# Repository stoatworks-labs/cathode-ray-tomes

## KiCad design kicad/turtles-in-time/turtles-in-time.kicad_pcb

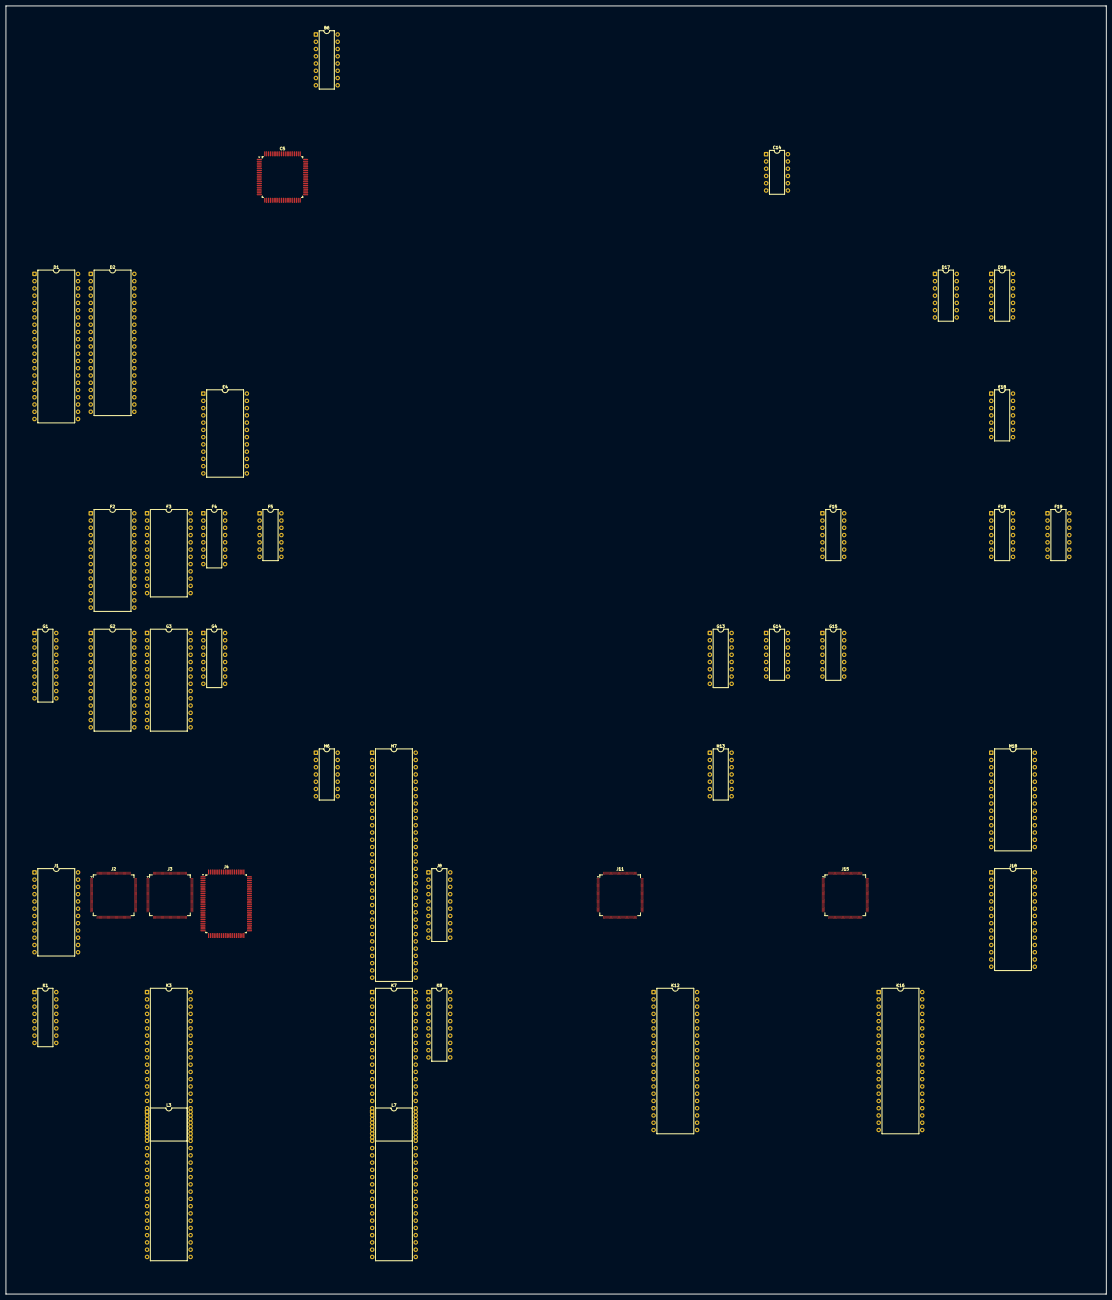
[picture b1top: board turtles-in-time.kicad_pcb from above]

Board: 2 copper layers, 385.2 x 450.9 mm, 43 parts (0 on the bottom side), 406 nets, no tracks yet.

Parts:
B6: YM3012; DIP-16_W7.62mm
C5: 053260; PQFP-80_14x14mm_P0.65mm
C14: MB3722; DIP-12_W7.62mm
D1: 065A08; DIP-42_W15.24mm
D2: Z80CPU; DIP-40_W15.24mm
D17: 74LS00; DIP-14_W7.62mm
D18: 74LS32; DIP-14_W7.62mm
E4: PAL20RS10; DIP-24_W15.24mm
E18: 74LS08; DIP-14_W7.62mm
F2: 27C512; DIP-28_W15.24mm
F3: CY7C128-45PC; DIP-24_W15.24mm
F4: 74LS157; DIP-16_W7.62mm
F5, F15: 74LS74; DIP-14_W7.62mm
F18, F19: 74LS04; DIP-14_W7.62mm
G1: 74LS245; DIP-20_W7.62mm
G2, G3: MB8464A-80-10-15/L-LL; DIP-28_W15.24mm
G4: 74LS157; DIP-16_W7.62mm
G13: 74LS138; DIP-16_W7.62mm
G14: 74LS74; DIP-14_W7.62mm
G15: 74LS08; DIP-14_W7.62mm
H6: LM324; DIP-14_W7.62mm
H7: DIP-64_W15.24mm
H13: 74LS07; DIP-14_W7.62mm
H18: MB8464A-10W-15W; DIP-28_W15.24mm
J1: HM6116P-3; DIP-24_W15.24mm
J2: 053245; TQFP-120_14x14mm_P0.4mm
J3: 053244; TQFP-120_14x14mm_P0.4mm
J4: 053251; PQFP-100_14x20mm_P0.65mm
J8: 74LS245; DIP-20_W7.62mm
J11: 051962; TQFP-120_14x14mm_P0.4mm
J15: 052109; TQFP-120_14x14mm_P0.4mm
J18: MB8464A-10W-15W; DIP-28_W15.24mm
K1: 74LS367; DIP-16_W7.62mm
K3, K7: 065A08; DIP-42_W15.24mm
K8: 74LS245; DIP-20_W7.62mm
K12, K16: 955D05-06-07-08; DIP-40_W15.24mm
L3, L7: 065A08; DIP-42_W15.24mm

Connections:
/M6: J2.10, J3.10, J4.41, J11.78
/M12: J2.12, J3.12, J11.95
/MAIN_A1: G4.2, G15.2, H7.30, J4.85, J11.88, J15.66
/MAIN_A2: G4.5, H7.29, J2.25, J3.18, J4.84, J11.89, J15.67
/MAIN_A3: G4.11, H7.28, J2.24, J3.17, J4.83, J15.68
/MAIN_A4: G4.14, H7.27, J2.23, J3.15, J4.82, J15.69
/MAIN_A5: F4.2, G15.5, H7.24, J15.116
/MAIN_A6: F4.5, G15.10, H7.23, J15.115
/MAIN_A7: H7.22, J2.22, J15.114
/MAIN_A8: G13.1, H7.21, J2.20, J15.113
/MAIN_A9: G13.2, H7.20, J2.19, J15.112
/MAIN_A10: G13.3, H7.19, J2.18, J15.111
/MAIN_A11: E18.9, G13.4, H7.17, J2.17, J15.110
/MAIN_A12: H7.16, J2.15, J15.109
/MAIN_A13: H7.15, J2.14, J15.80
/MAIN_A14: H7.14, J15.81
/MAIN_A15: H7.13, J15.82
/MAIN_DB0: C5.8, J3.29, J4.80, J11.79, J15.56
/MAIN_DB1: C5.9, J3.28, J4.79, J11.80, J15.57
/MAIN_DB2: C5.10, J3.27, J4.77, J11.81, J15.58
/MAIN_DB3: C5.11, J3.26, J4.76, J11.82, J15.59
/MAIN_DB4: C5.13, J3.25, J4.75, J11.83, J15.60
/MAIN_DB5: C5.14, J3.24, J4.74, J11.84, J15.62
/MAIN_DB6: C5.15, J3.23, J15.63
/MAIN_DB7: C5.16, J3.22, J11.86, J15.64
/MRW: D18.2, E18.12
/M~RD: F4.11, G1.1, J2.13, J3.20, J11.87, J15.85
/OBJ~SET: D17.1, E18.13, J2.6, J3.13
/PDS: E18.10, F15.4, G13.6
/RM~RD: J11.96, J15.97
/SCR~CLK: J11.90, J15.65
/colmix/ACOL0: J4.57, J11.30
/colmix/ACOL1: J4.58, J11.32
/colmix/ACOL2: J4.59, J11.33
/colmix/ACOL3: J4.60, J11.34
/colmix/APAL0: J4.61, J11.36
/colmix/APAL1: J4.62, J11.37
/colmix/APAL2: J4.63, J11.38
/colmix/BCOL0: J4.66, J11.46
/colmix/BCOL1: J4.67, J11.47
/colmix/BCOL2: J4.68, J11.48
/colmix/BCOL3: J4.69, J11.49
/colmix/BPAL0: J4.70, J11.51
/colmix/BPAL1: J4.71, J11.52
/colmix/BPAL2: J4.72, J11.53
/colmix/FCOL0: J4.47, J11.59
/colmix/FCOL1: J4.48, J11.60
/colmix/FCOL2: J4.49, J11.62
/colmix/FCOL3: J4.50, J11.63
/colmix/FPAL0: J4.51, J11.65
/colmix/FPAL1: J4.52, J11.66
/colmix/OCOL0: J3.120, J4.30
/colmix/OCOL1: J3.119, J4.31
/colmix/OCOL2: J3.118, J4.32
/colmix/OCOL3: J3.117, J4.33
/colmix/OCOL4: J3.116, J4.34
/colmix/OCOL5: J3.115, J4.35
/colmix/OCOL6: J3.114, J4.36
/colmix/OCOL7: J3.113, J4.37
/colmix/OCOL8: J3.112, J4.38
/colmix/PCU~CS: G13.7, J4.81
/colmix/PR12: J3.110, J4.25
/colmix/PR13: J3.109, J4.27
/colmix/SDI0: J3.108, J4.95
/main2obj/MPDS: D17.5, E18.8
/main2obj/RD0: G3.11, J2.45, K8.2
/main2obj/RD1: G3.12, J2.44, K8.3
/main2obj/RD2: G3.13, J2.43, K8.4
/main2obj/RD3: G3.15, J2.42, K8.5
/main2obj/RD4: G3.16, J2.40, K8.6
/main2obj/RD5: G3.17, J2.39, K8.7
/main2obj/RD6: G3.18, J2.38, K8.8
/main2obj/RD7: G3.19, J2.37, K8.9
/main2obj/RD8: G2.19, J2.35, J8.2
/main2obj/RD9: G2.18, J2.34, J8.3
/main2obj/RD10: G2.17, J2.33, J8.4
/main2obj/RD11: G2.16, J2.32, J8.5
/main2obj/RD12: G2.15, J2.30, J8.6
/main2obj/RD13: G2.13, J2.29, J8.7
/main2obj/RD14: G2.12, J2.28, J8.8
/main2obj/RD15: G2.11, J2.27, J8.9
/main2obj/RDB0: H7.31, K8.18
/main2obj/RDB1: H7.32, K8.17
/main2obj/RDB2: H7.33, K8.16
/main2obj/RDB3: H7.35, K8.15
/main2obj/RDB4: H7.36, K8.14
/main2obj/RDB5: H7.37, K8.13
/main2obj/RDB6: H7.38, K8.12
/main2obj/RDB7: H7.39, K8.11
/main2obj/RDB8: H7.40, J8.18
/main2obj/RDB9: H7.43, J8.17
/main2obj/RDB10: H7.44, J8.16
/main2obj/RDB11: H7.45, J8.15
/main2obj/RDB12: H7.46, J8.14
/main2obj/RDB13: H7.47, J8.13
/main2obj/RDB14: H7.48, J8.12
/main2obj/RDB15: H7.49, J8.11
/objects/AR0: J2.119, J3.30
/objects/AR1: J2.118, J3.32
/objects/AR2: J2.117, J3.33
/objects/AROK: J2.116, J3.34
/objects/BK0: G1.18, J1.9, K1.3, K3.36, K7.36, L3.36, L7.36
/objects/BK1: G1.17, J1.10, K1.5, K3.35, K7.35, L3.35, L7.35
/objects/BK2: G1.16, J1.11, K1.7, K3.34, K7.34, L3.34, L7.34
/objects/BK3: G1.15, J1.13, K1.9, K3.33, K7.33, L3.33, L7.33
/objects/BK4: G1.14, J1.14, K1.11, K3.2, K7.2, L3.2, L7.2
/objects/BK5: G1.13, J1.15, K1.13, K3.1, K7.1, L3.1, L7.1
/objects/BK6: F18.9, G1.12, J1.16
/objects/BK7: G1.11, J1.17
/objects/BR0: J2.115, J3.35
/objects/BR1: J2.114, J3.36
/objects/BR2: J2.113, J3.37
/objects/BROK: J2.112, J3.38
/objects/CLAT: J2.86, J3.64
/objects/HP0: J2.96, J3.54
/objects/HP1: J2.97, J3.53
/objects/HP2: J2.98, J3.52
/objects/HP3: J2.99, J3.50
/objects/HP4: J2.100, J3.49
/objects/HP5: J2.102, J3.48
/objects/HP6: J2.103, J3.47
/objects/HP7: J2.104, J3.45
/objects/HP8: J2.105, J3.44
/objects/HP9: J2.107, J3.43
/objects/HRFP: J2.110, J3.39
/objects/MDB6: L3.13, L7.13
/objects/OBJMPX: D17.9, F19.12, G15.1, G15.4, G15.9
/objects/OBJROMA0: J2.85, K3.10, K7.10, L3.10, L7.10
/objects/OBJROMA1: J2.84, K3.9, K7.9, L3.9, L7.9
/objects/OBJROMA2: J2.83, K3.8, K7.8, L3.8, L7.8
/objects/OBJROMA3: J2.82, K3.7, K7.7, L3.7, L7.7
/objects/OBJROMA4: J2.80, K3.6, K7.6, L3.6, L7.6
/objects/OBJROMA5: J2.79, K3.5, K7.5, L3.5, L7.5
/objects/OBJROMA6: J2.78, K3.4, K7.4, L3.4, L7.4
/objects/OBJROMA7: J2.77, K3.3, K7.3, L3.3, L7.3
/objects/OBJROMA8: J2.75, K3.41, K7.41, L3.41, L7.41
/objects/OBJROMA9: J2.74, K3.40, K7.40, L3.40, L7.40
/objects/OBJROMA10: J2.73, K3.39, K7.39, L3.39, L7.39
/objects/OBJROMA11: J2.72, K3.38, K7.38, L3.38, L7.38
/objects/OBJROMA12: J2.70, K3.37, K7.37, L3.37, L7.37
/objects/OBJROMA13: G4.3, J2.69, K1.2
/objects/OBJROMA14: G4.6, J2.68, K1.4
/objects/OBJROMA15: G4.10, J2.67, K1.6
/objects/OBJROMA16: G4.13, J2.66, K1.10
/objects/OBJROMA17: F4.3, J2.65, K1.12
/objects/OBJROMA18: F4.6, J2.64, K1.14
/objects/OBJROMD0: J3.100, K7.14, L7.14
/objects/OBJROMD1: J3.99, K7.16, L7.16
/objects/OBJROMD2: J3.98, K7.18, L7.18
/objects/OBJROMD3: J3.97, K7.20, L7.20
/objects/OBJROMD4: J3.96, K7.23, L7.23
/objects/OBJROMD5: J3.95, K7.25, L7.25
/objects/OBJROMD6: J3.94, K7.27, L7.27
/objects/OBJROMD7: J3.93, K7.29, L7.29
/objects/OBJROMD8: J3.92, K7.15, L7.15
/objects/OBJROMD9: J3.90, K7.17, L7.17
/objects/OBJROMD10: J3.89, K7.19, L7.19
/objects/OBJROMD11: J3.88, K7.21, L7.21
/objects/OBJROMD12: J3.87, K7.24, L7.24
/objects/OBJROMD13: J3.86, K7.26, L7.26
/objects/OBJROMD14: J3.85, K7.28, L7.28
/objects/OBJROMD15: J3.84, K7.30, L7.30
/objects/OBJROMD16: J3.83, K3.14, L3.14
/objects/OBJROMD17: J3.82, K3.16, L3.16
/objects/OBJROMD18: J3.80, K3.18, L3.18
/objects/OBJROMD19: J3.79, K3.20, L3.20
/objects/OBJROMD20: J3.78, K3.23, L3.23
/objects/OBJROMD21: J3.77, K3.25, L3.25
/objects/OBJROMD22: J3.75, K3.27, L3.27
/objects/OBJROMD23: J3.74, K3.29, L3.29
/objects/OBJROMD24: J3.73, K3.15, L3.15
/objects/OBJROMD25: J3.72, K3.17, L3.17
/objects/OBJROMD26: J3.70, K3.19, L3.19
/objects/OBJROMD27: J3.69, K3.21, L3.21
/objects/OBJROMD28: J3.68, K3.24, L3.24
/objects/OBJROMD29: J3.67, K3.26, L3.26
/objects/OBJROMD30: J3.66, K3.28, L3.28
/objects/OBJROMD31: J3.65, K3.30, L3.30
/objects/PL0: J2.87, J3.63
/objects/PL1: J2.88, J3.62
/objects/PL2: J2.89, J3.60
/objects/PL3: J2.90, J3.59
/objects/PL4: J2.92, J3.58
/objects/PL5: J2.93, J3.57
/objects/PL6: J2.94, J3.56
/objects/RA0: G2.10, G3.10, G15.3
/objects/RA1: G2.9, G3.9, J2.52
/objects/RA2: G2.8, G3.8, J2.53
/objects/RA3: G2.7, G3.7, J2.54
/objects/RA4: G2.6, G3.6, G15.6
/objects/RA5: G2.5, G3.5, G15.8
/objects/RA6: G2.4, G3.4, J2.55
/objects/RA7: G2.3, G3.3, J2.56
/objects/RA8: G2.25, G3.25, J2.57
/objects/RA9: G2.24, G3.24, J2.58
/objects/RA10: G2.21, G3.21, J2.59
/objects/RA11: G2.23, G3.23, J2.62
/objects/RA12: G2.2, G3.2, J2.63
/objects/R~OE: G2.22, G3.22, J2.49
/objects/SHADOW: J2.95, J3.55
/objects/~BK6: F18.8, K3.13
/objects/~HIT: J2.108, J3.42
/objects/~WE1: G2.27, J2.48
/objects/~WE2: G3.27, J2.47
/objects/~ZLD: J2.109, J3.40
/pcm_snd/AUX2: C5.24, D1.13
/pcm_snd/PCM~CS: C5.72, E4.19
/pcm_snd/RA0: C5.39, D1.30
/pcm_snd/RA1: C5.40, D1.10
/pcm_snd/RA2: C5.41, D1.9
/pcm_snd/RA3: C5.42, D1.8
/pcm_snd/RA4: C5.44, D1.7
/pcm_snd/RA5: C5.45, D1.6
/pcm_snd/RA6: C5.46, D1.5
/pcm_snd/RA8: C5.48, D1.3
/pcm_snd/RA9: C5.49, D1.41
/pcm_snd/RA10: C5.50, D1.40
/pcm_snd/RA11: C5.51, D1.39
/pcm_snd/RA12: C5.53, D1.38
/pcm_snd/RA13: C5.54, D1.37
/pcm_snd/RA14: C5.55, D1.36
/pcm_snd/RA15: C5.56, D1.35
/pcm_snd/RA16: C5.57, D1.34
/pcm_snd/RA17: C5.58, D1.33
/pcm_snd/RA20: C5.62, D1.42
/pcm_snd/RD0: C5.29, D1.14
/pcm_snd/RD1: C5.30, D1.16
/pcm_snd/RD2: C5.31, D1.18
/pcm_snd/RD3: C5.32, D1.20
/pcm_snd/RD4: C5.35, D1.23
/pcm_snd/RD5: C5.36, D1.25
/pcm_snd/RD6: C5.37, D1.27
/pcm_snd/RD7: C5.38, D1.29
/pcm_snd/SH1: B6.6, C5.26, F5.11
/pcm_snd/SH2: B6.5, C5.27
/pcm_snd/SND_A0: C5.70, D2.30, E4.8, F2.10, F3.8
/pcm_snd/SND_A1: C5.69, D2.31, E4.7, F2.9, F3.7
/pcm_snd/SND_A2: C5.68, D2.32, E4.6, F2.8, F3.6
/pcm_snd/SND_A3: C5.67, D2.33, F2.7, F3.5
/pcm_snd/SND_A4: C5.66, D2.34, F2.6, F3.4
/pcm_snd/SND_A5: C5.65, D2.35, F2.5, F3.3
/pcm_snd/SND_D0: C5.5, F2.11, F3.9
/pcm_snd/SND_D1: C5.4, F2.12, F3.10
/pcm_snd/SND_D2: C5.3, D2.12, F2.13, F3.11
/pcm_snd/SND_D3: C5.2, D2.8, D2.14, F2.15, F3.13
/pcm_snd/SND_D4: C5.1, D2.15, F2.16, F3.14
/pcm_snd/SND_D5: C5.80, D2.9, F2.17, F3.15
/pcm_snd/SND_D6: C5.79, D2.10, F2.18, F3.16
/pcm_snd/SND_D7: C5.78, D2.13, D2.18, F2.19, F3.17
/pcm_snd/SY: B6.2, C5.25
/scroll/COL5: J11.109, J15.42
/scroll/COL6: J11.108, J15.43
/scroll/COL7: J11.107, J15.46
/scroll/GFXROMA0: J15.35, K12.9, K16.9
/scroll/GFXROMA1: J15.34, K12.8, K16.8
/scroll/GFXROMA2: J15.33, K12.7, K16.7
/scroll/GFXROMA3: J15.32, K12.6, K16.6
/scroll/GFXROMA4: J15.30, K12.5, K16.5
/scroll/GFXROMA5: J15.29, K12.4, K16.4
/scroll/GFXROMA6: J15.28, K12.3, K16.3
/scroll/GFXROMA7: J15.27, K12.2, K16.2
/scroll/GFXROMA8: J15.26, K12.40, K16.40
/scroll/GFXROMA9: J15.25, K12.39, K16.39
/scroll/GFXROMA10: J15.24, K12.38, K16.38
/scroll/GFXROMA11: J15.37, K12.37, K16.37
/scroll/GFXROMA12: J15.38, K12.36, K16.36
/scroll/GFXROMA13: J15.41, K12.35, K16.35
/scroll/GFXROMA14: J15.39, K12.34, K16.34
/scroll/GFXROMA15: J15.40, K12.33, K16.33
/scroll/GFXROMA16: J15.23, K12.32, K16.32
/scroll/GFXROMA17: J15.22, K12.1, K16.1
/scroll/GFXROMD0: J11.29, K16.13
/scroll/GFXROMD1: J11.28, K16.15
/scroll/GFXROMD2: J11.27, K16.17
/scroll/GFXROMD3: J11.26, K16.19
/scroll/GFXROMD4: J11.25, K16.22
/scroll/GFXROMD5: J11.24, K16.24
/scroll/GFXROMD6: J11.23, K16.26
/scroll/GFXROMD7: J11.22, K16.28
/scroll/GFXROMD8: J11.21, K16.14
/scroll/GFXROMD9: J11.20, K16.16
/scroll/GFXROMD10: J11.19, K16.18
/scroll/GFXROMD11: J11.18, K16.20
/scroll/GFXROMD12: J11.17, K16.23
/scroll/GFXROMD13: J11.16, K16.25
/scroll/GFXROMD14: J11.13, K16.27
/scroll/GFXROMD15: J11.12, K16.29
/scroll/GFXROMD16: J11.11, K12.13
/scroll/GFXROMD17: J11.10, K12.15
/scroll/GFXROMD18: J11.9, K12.17
/scroll/GFXROMD19: J11.8, K12.19
/scroll/GFXROMD20: J11.7, K12.22
/scroll/GFXROMD21: J11.6, K12.24
/scroll/GFXROMD22: J11.5, K12.26
/scroll/GFXROMD23: J11.4, K12.28
/scroll/GFXROMD24: J11.3, K12.14
/scroll/GFXROMD25: J11.2, K12.16
/scroll/GFXROMD26: J11.120, K12.18
/scroll/GFXROMD27: J11.119, K12.20
/scroll/GFXROMD28: J11.118, K12.23
/scroll/GFXROMD29: J11.117, K12.25
/scroll/GFXROMD30: J11.116, K12.27
/scroll/GFXROMD31: J11.115, K12.29
/scroll/SCRAMA0: H18.10, J15.2, J18.10
/scroll/SCRAMA1: H18.9, J15.120, J18.9
/scroll/SCRAMA2: H18.8, J15.119, J18.8
/scroll/SCRAMA3: H18.7, J15.118, J18.7
/scroll/SCRAMA4: H18.6, J15.117, J18.6
/scroll/SCRAMA5: H18.5, J15.70, J18.5
/scroll/SCRAMA6: H18.4, J15.71, J18.4
/scroll/SCRAMA7: H18.3, J15.72, J18.3
/scroll/SCRAMA8: H18.25, J15.73, J18.25
/scroll/SCRAMA9: H18.24, J15.76, J18.24
/scroll/SCRAMA10: H18.21, J15.77, J18.21
/scroll/SCRAMA11: H18.23, J15.78, J18.23
/scroll/SCRAMA12: H18.2, J15.79, J18.2
/scroll/VD0: H18.11, J15.20
/scroll/VD1: H18.12, J15.19
/scroll/VD2: H18.13, J15.18
/scroll/VD3: H18.15, J15.17
/scroll/VD4: H18.16, J15.16
/scroll/VD5: H18.17, J15.13
/scroll/VD6: H18.18, J15.12
/scroll/VD7: H18.19, J15.11
/scroll/VD8: J15.10, J18.11
/scroll/VD9: J15.9, J18.12
/scroll/VD10: J15.8, J18.13
/scroll/VD11: J15.7, J18.15
/scroll/VD12: J15.6, J18.16
/scroll/VD13: J15.5, J18.17
/scroll/VD14: J15.4, J18.18
/scroll/VD15: J15.3, J18.19
/scroll/ZA1H: J11.101, J15.50
/scroll/ZA2H: J11.100, J15.51
/scroll/ZA4H: J11.99, J15.52
/scroll/ZB1H: J11.106, J15.47
/scroll/ZB2H: J11.103, J15.48
/scroll/ZB4H: J11.102, J15.49
/scroll/~BE: J11.98, J15.53
/scroll/~RCS1: J15.93, J18.20
/scroll/~ROE1: J15.95, J18.22
/scroll/~ROE2: H18.22, J15.96
/scroll/~RWE1: J15.107, J18.27
/scroll/~RWE2: H18.27, J15.108
/sound/ROM~OE: E4.16, F2.22
/sound/SND_A6: D2.36, F2.4, F3.2
/sound/SND_A7: D2.37, F2.3, F3.1
/sound/SND_A8: D2.38, F2.25, F3.23
/sound/SND_A9: D2.39, E4.14, F2.24, F3.22
/sound/SND_A10: D2.40, E4.13, F2.21, F3.19
/sound/SND_A11: E4.11, F2.23
/sound/SND_A12: D2.2, E4.9, F2.2
/sound/SND_A14: D2.4, F2.27
/sound/SRAM~CE: E4.17, F3.18
/sound/S~CLK: G14.5, G14.11
/sound/S~IORQ: D2.20, G15.13
/sound/S~RD: D2.6, D2.21, F3.20, F19.3
/sound/S~WR: D2.5, E4.5, F3.21
/sound/~M1: D2.27, E4.3
/sound/~RFSH: D2.28, E4.2
/sound/~WAIT: D2.24, G14.9
/sound/~WSET: E4.15, G14.10
/~AS: E4.4, H7.1
/~HSYNC: J2.4, J3.8, J11.73
/~LDS: H7.63, J2.9
/~OBJ: D17.2, D18.1, E4.21
/~OVRC: F4.1, G1.19, G4.1, G13.10
/~RESET: J2.3, J3.3, J11.92, J15.55
/~SYSRES: B6.7, C5.75, D2.3, D2.26, F5.13, G15.12, H7.59, H13.8
/~UDS: H7.62, J2.8, J3.19
/~VRAM: J11.97, J15.54, J15.84
/~VSYNC: J2.5, J3.9, J11.72
GND: E4.10, E4.12, F15.2
unnamed: B6.14, H6.2
unnamed: B6.12, H6.10
unnamed: B6.9, B6.10, H6.5, H6.12
unnamed: B6.13, H6.1
unnamed: B6.15, H6.3
unnamed: C5.71, F19.4
unnamed: D2.7, E4.18
unnamed: D2.16, F5.6
unnamed: D2.17, F5.9
unnamed: D17.3, D17.10
unnamed: E4.1, F15.5
unnamed: F4.4, J1.4
unnamed: F4.7, J1.3
unnamed: F4.9, J1.20
unnamed: F4.12, J1.21
unnamed: F5.1, G15.11
unnamed: G4.4, J1.8
unnamed: G4.7, J1.7
unnamed: G4.9, J1.6
unnamed: G4.12, J1.5
unnamed: G14.2, G14.6
unnamed: G14.8, G14.12
unnamed: H6.6, H6.7
unnamed: H6.8, H6.9
unnamed: H6.13, H6.14
unnamed: D17.6, H7.54
unnamed: H13.9, J15.98
unnamed: F19.13, J2.26
unnamed: D18.3, J2.7
unnamed: E18.11, J8.1, K8.1
unnamed: D17.8, J8.19, K8.19
VCC: B6.1, C5.20, C5.33, C5.73, D1.4, D1.11, D1.22, D1.31, D2.22, E4.20, E4.24, F2.28, F3.24, F4.13, F5.2, F5.4, F15.1, G2.26, G2.28, G3.26, G3.28, G14.1, G14.4, G14.13, H7.9, H7.26, H7.41, H7.58, H18.26, H18.28, J1.24, J2.16, J2.46, J2.60, J2.76, J2.106, J2.120, J3.16, J3.46, J3.76, J3.106, J4.1, J4.2, J4.3, J4.28, J4.29, J4.39, J4.42, J4.43, J4.44, J4.45, J4.46, J4.53, J4.78, J4.97, J4.98, J4.99, J4.100, J11.14, J11.44, J11.74, J11.104, J15.14, J15.44, J15.74, J15.104, J18.26, J18.28, K1.16, K3.22, K3.31, K3.32, K7.22, K7.31, K7.32, K12.21, K12.31, K16.21, K16.31, L3.22, L3.31, L3.32, L7.22, L7.31, L7.32
VSS: B6.3, B6.8, B6.16, C5.12, C5.34, C5.43, C5.52, C5.61, C5.74, C14.6, C14.7, D1.1, D1.2, D1.12, D1.32, D2.1, D2.11, D2.29, F2.14, F3.12, F4.10, F4.15, F5.12, G2.14, G2.20, G3.14, G3.20, G4.15, H7.2, H7.10, H7.18, H7.25, H7.34, H7.42, H7.50, H7.55, H7.57, H18.14, H18.20, J1.12, J1.18, J1.19, J1.22, J2.1, J2.2, J2.11, J2.21, J2.31, J2.41, J2.51, J2.61, J2.71, J2.81, J2.91, J2.101, J2.111, J3.1, J3.2, J3.4, J3.5, J3.6, J3.7, J3.11, J3.21, J3.31, J3.41, J3.51, J3.61, J3.71, J3.81, J3.91, J3.101, J3.111, J4.4, J4.5, J4.6, J4.7, J4.8, J4.9, J4.10, J4.15, J4.20, J4.21, J4.22, J4.23, J4.24, J4.40, J4.55, J4.56, J4.64, J4.65, J4.73, J4.90, J4.94, J11.1, J11.15, J11.31, J11.45, J11.61, J11.75, J11.91, J11.94, J11.105, J11.110, J11.111, J11.112, J11.113, J11.114, J15.1, J15.15, J15.21, J15.31, J15.36, J15.45, J15.61, J15.75, J15.91, J15.105, J18.14, K1.1, K1.8, K1.15, K3.11, K3.12, K7.11, K7.12, K12.10, K12.11, K12.12, K12.30, K16.10, K16.11, K16.12, K16.30, L3.11, L3.12, L7.11, L7.12

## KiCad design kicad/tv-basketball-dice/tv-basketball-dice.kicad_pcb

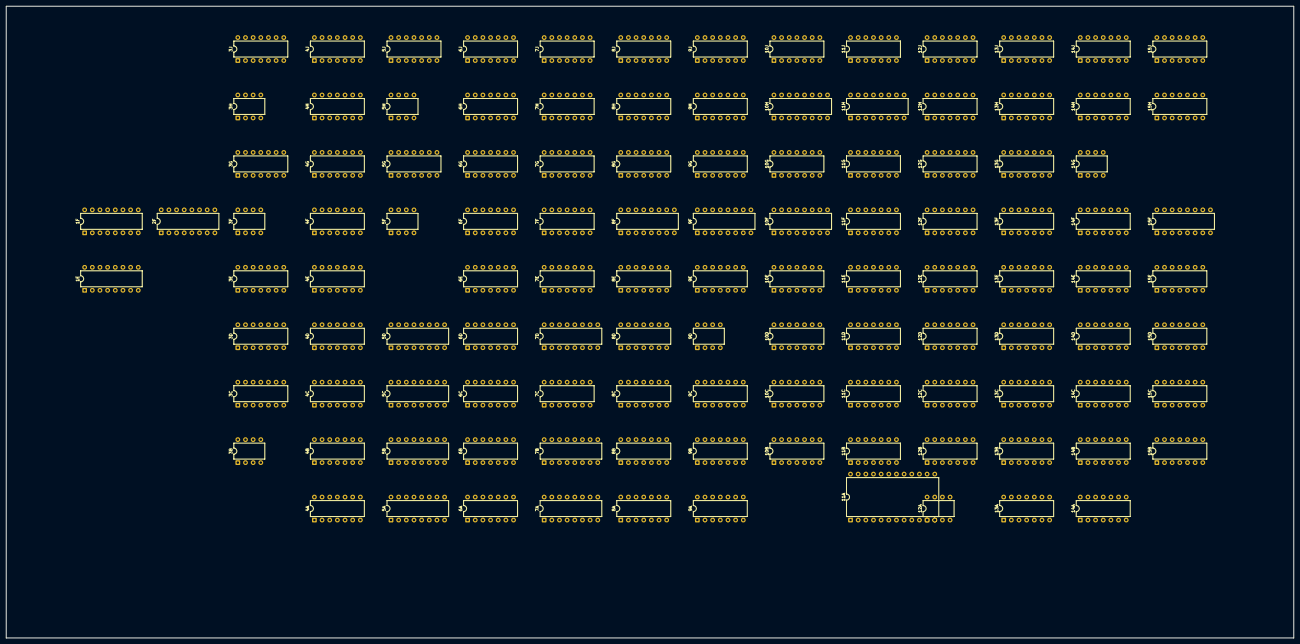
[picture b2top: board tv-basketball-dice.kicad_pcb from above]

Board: 2 copper layers, 427.0 x 209.5 mm, 115 parts (0 on the bottom side), 350 nets, no tracks yet.

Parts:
1E, 1F: 74155; DIP-16_W7.62mm
2F, 5A, 5B, 5C, 5D: 74151; DIP-16_W7.62mm
3B, 3F, 3H, 5F, 5H, 9D, 12A, 14G: 555; DIP-8_W7.62mm
3C, 6J, 8E, 9B, 9J, 10B, 10J, 11E, 13B, 14E: 7402; DIP-14_W7.62mm
3D, 8D, 11B, 12B: 7427; DIP-14_W7.62mm
3E, 4B, 6E, 7E, 12F, 12J, 13A, 13E, 15D, 15J: 7404; DIP-14_W7.62mm
3G, 5G, 9E, 10D, 10E, 12D, 13C, 13F, 13G, 13H, 14B, 15C, 15E: 7400; DIP-14_W7.62mm
3J, 4J, 8G, 8H, 12G, 13D: 7474; DIP-14_W7.62mm
4A, 11C: 7408; DIP-14_W7.62mm
4C, 4D, 4E, 7F, 7G, 7H: 7454; DIP-14_W7.62mm
4F, 4H, 6F, 6H, 11D, 11F, 11G, 14H, 15H: 7493; DIP-14_W7.62mm
4G, 6G, 10G: 7420; DIP-14_W7.62mm
5J, 9G, 9H: 7486; DIP-14_W7.62mm
6A, 6B, 6C, 6D: 7490; DIP-14_W7.62mm
7A: 7448; DIP-16_W7.62mm
7B, 7D: 74192; DIP-16_W7.62mm
7C, 14C, 14D, 15B: 7425; DIP-14_W7.62mm
7J, 9C, 11J, 12E, 14A, 14J: 74107; DIP-14_W7.62mm
8A, 8B, 8C, 10C, 12H, 14F: 7410; DIP-14_W7.62mm
8F: 7483; DIP-16_W7.62mm
8J: 7451; DIP-14_W7.62mm
9A, 13J: 7430; DIP-14_W7.62mm
9F, 10F, 10H, 11H: 74161; DIP-16_W7.62mm
11A: 74154; DIP-24_W15.24mm
12C: 7432; DIP-14_W7.62mm
15F: 74279; DIP-16_W7.62mm

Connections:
1F-2: 1F.2, 1F.14, 10C.6, 12B.13, 13E.13
2F-5: 2F.5, 6J.9
2F-9: 2F.9, 5J.8
2F-10: 2F.10, 5J.11
2F-11: 2F.11, 5J.3
3B-3: 3B.3, 4B.5
3C-1: 3C.1, 4B.11
3C-2: 3C.2, 11B.12
3C-3: 3C.3, 3D.12
3C-4: 3C.4, 4B.13
3C-5: 3C.5, 11B.6
3C-6: 3C.6, 3D.6
3C-8: 3C.8, 3J.5, 12A.2
3C-9: 3C.9, 3J.8
3C-10: 3C.10, 4J.2
3D-1: 3D.1, 11B.1
3D-2: 3D.2, 3G.3
3D-3: 3D.3, 3E.4
3D-4: 3D.4, 3G.11
3D-5: 3D.5, 11B.5, 14B.11
3D-13: 3D.13, 3E.10
3E-2: 3E.2, 3J.3
3E-3: 3E.3, 4A.11, 4C.2, 4D.2, 4E.2, 7F.2, 7G.2, 7H.2
3E-5: 3E.5, 10B.13, 11B.13
3E-6: 3E.6, 4C.1, 4D.1, 4E.1, 7F.1, 7G.1, 7H.1
3E-8: 3E.8, 3G.1
3E-9: 3E.9, 3F.3, 4F.2, 4F.3
3E-11: 3E.11, 4A.8, 4C.4, 4D.4, 4E.4, 7F.4, 7G.4, 7H.4
3E-12: 3E.12, 3G.13
3E-13: 3E.13, 3H.3, 4H.2, 4H.3
3F-2: 3F.2, 3H.2, 5F.2, 5H.2, 10C.12, 11B.10
3G-2: 3G.2, 3G.4, 4G.6
3G-6: 3G.6, 4F.14
3G-8: 3G.8, 4H.14
3G-10: 3G.10, 3G.12, 4G.8
3J-2: 3J.2, 3J.9
4A-1: 4A.1, 4A.9, 9B.10
4A-2: 4A.2, 4A.5, 4B.1, 4J.6
4A-3: 4A.3, 10B.12
4A-4: 4A.4, 4A.12, 9B.4
4A-6: 4A.6, 10B.2
4A-10: 4A.10, 4A.13, 4B.2
4B-8: 4B.8, 4C.9, 4D.9, 4E.9, 7F.9, 7G.9, 7H.9
4B-9: 4B.9, 10B.1, 11B.3
4B-10: 4B.10, 11C.2
4B-12: 4B.12, 11C.5
4C-3: 4C.3, 4G.12, 4H.11, 7F.3
4C-5: 4C.5, 4F.11, 4G.2, 7F.5
4C-8: 4C.8, 7E.11
4C-10: 4C.10, 6G.12, 6H.11, 7F.10
4C-13: 4C.13, 6F.11, 6G.2, 7F.13
4D-3: 4D.3, 4G.9, 4H.8, 7G.3
4D-5: 4D.5, 4F.8, 4G.5, 7G.5
4D-8: 4D.8, 7E.1
4D-10: 4D.10, 6G.9, 6H.8, 7G.10
4D-13: 4D.13, 6F.8, 6G.5, 7G.13
4E-3: 4E.3, 4G.10, 4H.9, 7H.3
4E-5: 4E.5, 4F.9, 4G.4, 7H.5
4E-8: 4E.8, 7E.13
4E-10: 4E.10, 6G.10, 6H.9, 7H.10
4E-13: 4E.13, 6F.9, 6G.4, 7H.13
4F-1: 4F.1, 4F.12, 4G.1
4G-13: 4G.13, 4H.1, 4H.12
5A-1: 5A.1, 6D.12
5A-2: 5A.2, 6B.1, 6B.12
5A-3: 5A.3, 7B.3, 7C.2
5A-4: 5A.4, 7C.12, 7D.3
5A-5: 5A.5, 7A.7
5A-12: 5A.12, 9C.2
5A-14: 5A.14, 6C.12
5A-15: 5A.15, 6A.1, 6A.12
5B-1: 5B.1, 6D.9
5B-2: 5B.2, 6B.9
5B-3: 5B.3, 7B.2, 7C.1
5B-4: 5B.4, 7C.13, 7D.2
5B-5: 5B.5, 7A.1
5B-14: 5B.14, 6C.9
5B-15: 5B.15, 6A.9
5C-1: 5C.1, 6D.8
5C-2: 5C.2, 6B.8
5C-3: 5C.3, 7B.6, 7C.4
5C-4: 5C.4, 7C.10, 7D.6
5C-5: 5C.5, 7A.2
5C-14: 5C.14, 6C.8
5C-15: 5C.15, 6A.8
5D-1: 5D.1, 6B.14, 6D.11
5D-2: 5D.2, 6B.11
5D-3: 5D.3, 7B.7, 7C.5
5D-4: 5D.4, 7C.9, 7D.7
5D-5: 5D.5, 7A.6
5D-14: 5D.14, 6A.14, 6C.11
5D-15: 5D.15, 6A.11
5F-3: 5F.3, 6E.11, 6F.2, 6F.3
5G-1: 5G.1, 6E.10
5G-2: 5G.2, 5G.4, 6G.6
5G-3: 5G.3, 11B.2
5G-6: 5G.6, 6F.14
5G-8: 5G.8, 6H.14
5G-10: 5G.10, 5G.12, 6G.8
5G-11: 5G.11, 11B.4
5G-13: 5G.13, 6E.8
5H-3: 5H.3, 6E.9, 6H.2, 6H.3
5J-6: 5J.6, 6E.13, 6J.5
6C-1: 6C.1, 8E.1
6D-1: 6D.1, 8E.13
6E-5: 6E.5, 9F.1, 10D.6, 10F.1, 10H.1, 11H.1, 11J.13
6E-6: 6E.6, 8D.1
6E-12: 6E.12, 6J.11
6F-1: 6F.1, 6F.12, 6G.1
6G-13: 6G.13, 6H.1, 6H.12
6J-1: 6J.1, 6J.8
6J-2: 6J.2, 6J.13
6J-3: 6J.3, 6J.4
6J-6: 6J.6, 11A.14, 13E.3
6J-10: 6J.10, 7J.12, 13G.13, 14C.5
6J-12: 6J.12, 8H.9
7A-5: 7A.5, 9E.3
7A-9: 7A.9, 8A.11
7A-10: 7A.10, 8A.1
7A-11: 7A.11, 8A.3
7A-12: 7A.12, 8B.11
7A-13: 7A.13, 8B.1
7A-14: 7A.14, 8B.3
7A-15: 7A.15, 8C.3
7B-4: 7B.4, 8D.12
7B-13: 7B.13, 7D.4
7C-6: 7C.6, 8C.1
7C-8: 7C.8, 8C.13
7D-13: 7D.13, 7E.3
7E-4: 7E.4, 9C.12
7E-5: 7E.5, 8C.8
7E-6: 7E.6, 8A.13, 8B.5
7E-8: 7E.8, 8D.13, 10B.9, 12B.10, 13A.13
7E-9: 7E.9, 8C.12
7F-8: 7F.8, 8H.2
7G-8: 7G.8, 8G.12
7H-8: 7H.8, 8G.2
7J-2: 7J.2, 12B.2, 13B.2, 13B.5
7J-5: 7J.5, 8J.4, 9G.2, 9G.13
7J-6: 7J.6, 8J.3
7J-8: 7J.8, 7J.11, 10J.13, 13E.1, 14A.8
7J-9: 7J.9, 13F.8
7J-10: 7J.10, 13C.8, 15C.10
8A-5: 8A.5, 8B.9, 8E.4
8A-6: 8A.6, 9A.1
8A-8: 8A.8, 9A.3
8A-9: 8A.9, 8C.4, 8D.8
8A-12: 8A.12, 9A.2
8B-6: 8B.6, 9A.4
8B-8: 8B.8, 9A.6
8B-12: 8B.12, 9A.5
8B-13: 8B.13, 8D.6
8C-2: 8C.2, 9C.3
8C-6: 8C.6, 9A.12
8D-2: 8D.2, 9D.3
8E-2: 8E.2, 13E.8
8E-3: 8E.3, 8E.12, 9E.11
8E-6: 8E.6, 9E.6
8E-11: 8E.11, 13E.9, 15F.4
8F-2: 8F.2, 9F.5
8F-3: 8F.3, 8F.11, 8J.6, 13F.4
8F-6: 8F.6, 9F.4
8F-8: 8F.8, 9G.11
8F-9: 8F.9, 9F.3
8F-10: 8F.10, 9G.3
8F-15: 8F.15, 9F.6
8G-1: 8G.1, 8G.13, 8H.1, 10J.10
8G-3: 8G.3, 8G.11, 8H.3, 15C.8
8G-5: 8G.5, 9G.1
8G-9: 8G.9, 9G.12
8H-5: 8H.5, 8J.5
8H-6: 8H.6, 8J.2
8H-8: 8H.8, 15E.1
8H-12: 8H.12, 11A.4, 14D.1
8J-1: 8J.1, 9H.11, 9J.9
8J-8: 8J.8, 12J.9
8J-9: 8J.9, 9H.3, 9J.12
8J-10: 8J.10, 9H.6, 9J.11
8J-13: 8J.13, 9H.8, 9J.8
9A-8: 9A.8, 10D.1, 11C.10
9B-1: 9B.1, 10B.3
9B-2: 9B.2, 11A.5
9B-5: 9B.5, 11A.10
9B-8: 9B.8, 11A.8, 11C.13
9B-11: 9B.11, 11A.13
9B-13: 9B.13, 10B.11
9E-2: 9E.2, 11A.9, 11C.12
9E-8: 9E.8, 9F.9, 10F.9
9E-9: 9E.9, 10F.15, 10G.13
9E-10: 9E.10, 9F.15, 10F.7
9E-12: 9E.12, 10J.8, 11E.12, 15F.9
9F-10: 9F.10, 11E.1, 11E.5
9F-11: 9F.11, 10G.12, 13G.1
9F-12: 9F.12, 9H.1, 9H.5, 12J.13, 13G.10
9F-13: 9F.13, 9H.4
9F-14: 9F.14, 9H.2
9G-6: 9G.6, 11B.9, 12B.3
9H-9: 9H.9, 10H.14
9H-10: 9H.10, 9H.13, 10H.12
9H-12: 9H.12, 10H.13
9J-1: 9J.1, 9J.5
9J-2: 9J.2, 9J.13
9J-3: 9J.3, 9J.10
9J-4: 9J.4, 10J.2
9J-6: 9J.6, 12J.8
10B-6: 10B.6, 10C.8, 12B.5
10B-8: 10B.8, 12B.11
10D-2: 10D.2, 12B.6, 13D.11
10D-4: 10D.4, 13D.8
10D-8: 10D.8, 13A.11, 15E.10
10D-9: 10D.9, 11A.6
10D-10: 10D.10, 11A.11
10E-1: 10E.1, 13D.5
10E-2: 10E.2, 10E.13, 11E.13, 12E.11
10E-3: 10E.3, 10E.9
10E-4: 10E.4, 12E.1, 12E.5
10E-5: 10E.5, 12E.3
10E-6: 10E.6, 12F.1
10E-8: 10E.8, 10H.3
10E-10: 10E.10, 10E.11, 10H.4
10E-12: 10E.12, 13D.2, 13D.6
10F-14: 10F.14, 13G.4
10G-8: 10G.8, 10J.6
10G-9: 10G.9, 11H.15, 11J.12, 12H.1
10G-10: 10G.10, 10H.11
10H-9: 10H.9, 11H.9, 12H.12
10H-15: 10H.15, 11H.7, 12H.13
10J-3: 10J.3, 10J.12, 12J.10
10J-4: 10J.4, 12J.11
10J-5: 10J.5, 11J.2
10J-9: 10J.9, 15D.8
10J-11: 10J.11, 12J.12
11A-15: 11A.15, 14D.12
11B-8: 11B.8, 11C.9
11B-11: 11B.11, 11C.11
11C-3: 11C.3, 12C.2, 12C.10
11C-6: 11C.6, 12C.1, 12C.4
11C-8: 11C.8, 14C.13
11D-1: 11D.1, 11D.12
11D-8: 11D.8, 12C.13, 12D.1
11D-9: 11D.9, 12C.12, 12D.2
11D-14: 11D.14, 13G.2, 15C.11
11E-10: 11E.10, 12E.9, 12E.12
11E-11: 11E.11, 12F.2
11F-14: 11F.14, 12G.6, 12G.11, 14H.2, 14H.3, 15H.2, 15H.3
11J-3: 11J.3, 12H.2
11J-10: 11J.10, 12G.9, 13F.10
12A-3: 12A.3, 12B.9
12B-1: 12B.1, 13B.13
12B-4: 12B.4, 13A.10
12B-8: 12B.8, 13D.12, 13D.13
12B-12: 12B.12, 13F.12, 14C.1
12C-3: 12C.3, 14C.12
12C-5: 12C.5, 14D.6, 14E.9
12C-6: 12C.6, 13C.1
12C-8: 12C.8, 13C.12
12C-9: 12C.9, 14D.8, 14E.8
12C-11: 12C.11, 12D.5, 12D.12
12D-3: 12D.3, 12D.4
12D-6: 12D.6, 12D.9
12D-8: 12D.8, 12E.10
12D-11: 12D.11, 12E.13
12G-2: 12G.2, 13J.8
12G-5: 12G.5, 13H.5, 14J.13
12G-12: 12G.12, 12H.8
12H-4: 12H.4, 12J.4
13A-8: 13A.8, 14C.9
13A-9: 13A.9, 14C.6
13B-1: 13B.1, 14C.2
13B-3: 13B.3, 14B.6
13B-6: 13B.6, 14B.3
13B-11: 13B.11, 13F.13, 15B.8
13B-12: 13B.12, 14F.9, 15B.6
13C-3: 13C.3, 13C.4, 13D.1
13C-5: 13C.5, 13C.11, 13D.4
13C-6: 13C.6, 13C.9, 15D.1
13C-10: 13C.10, 15C.3
13D-3: 13D.3, 13G.9, 14G.3
13E-2: 13E.2, 14A.11
13E-4: 13E.4, 15E.5
13E-5: 13E.5, 14F.6
13E-6: 13E.6, 15E.2, 15E.4
13E-10: 13E.10, 13F.5, 14F.3
13E-11: 13E.11, 13F.11, 15F.6
13E-12: 13E.12, 14F.10
13F-1: 13F.1, 14F.12
13F-6: 13F.6, 13F.9
13G-3: 13G.3, 14F.13
13G-5: 13G.5, 14A.5
13G-6: 13G.6, 14F.1
13G-8: 13G.8, 14F.2
13G-11: 13G.11, 14G.2
13H-2: 13H.2, 13H.11
14C-4: 14C.4, 14E.13, 15C.4
14C-8: 14C.8, 15D.11
14E-10: 14E.10, 14E.11, 15D.13
14E-12: 14E.12, 15C.1, 15F.7
14F-5: 14F.5, 15F.13
14F-8: 14F.8, 15F.15
15C-2: 15C.2, 15D.12
15C-6: 15C.6, 15D.9
15C-9: 15C.9, 15D.6
15C-12: 15C.12, 15D.4
15C-13: 15C.13, 15D.2
15E-3: 15E.3, 15F.2, 15F.3, 15F.11
15E-6: 15E.6, 15F.1, 15F.12
15E-8: 15E.8, 15F.14
15E-11: 15E.11, 15F.10
+5V: 1E.16, 1F.16, 2F.16, 3B.8, 3C.14, 3D.14, 3E.14, 3F.8, 3G.14, 3H.8, 3J.14, 4A.14, 4B.14, 4F.5, 4G.14, 4H.5, 4J.14, 5A.16, 5B.16, 5C.16, 5D.16, 5F.8, 5G.14, 5H.8, 5J.14, 6A.5, 6B.5, 6C.5, 6D.5, 6E.14, 6F.5, 6G.14, 6H.5, 6J.14, 7A.16, 7B.16, 7D.16, 7E.14, 7J.14, 8A.14, 8B.14, 8C.14, 8D.14, 8E.14, 8F.5, 8G.14, 8H.14, 9A.14, 9B.14, 9C.14, 9D.8, 9E.14, 9F.16, 9G.14, 9H.14, 9J.14, 10B.14, 10C.14, 10D.14, 10E.14, 10F.16, 10G.14, 10H.16, 10J.14, 11A.24, 11B.14, 11C.14, 11D.5, 11E.14, 11F.5, 11G.5, 11H.16, 11J.14, 12A.8, 12B.14, 12C.14, 12D.14, 12E.14, 12F.14, 12G.14, 12H.14, 12J.14, 13A.14, 13B.14, 13C.14, 13D.14, 13E.14, 13F.14, 13G.14, 13H.14, 13J.14, 14A.14, 14B.14, 14E.14, 14F.14, 14G.8, 14H.5, 14J.14, 15C.14, 15D.14, 15E.14, 15F.16, 15H.5, 15J.14
A: 3J.11, 4B.6, 4J.3, 7B.11, 7D.11, 9C.13, 10H.6, 11H.6, 11H.10, 11J.4, 11J.8, 11J.11, 12E.8, 12G.13, 13A.3, 13J.2, 13J.3, 13J.12, 14J.1, 14J.4, 14J.8, 14J.10, 14J.11
B: 6A.2, 6A.3, 6B.2, 6B.3, 6C.2, 6C.3, 6D.2, 6D.3, 13A.4
BALL: 10J.1, 13C.2, 13C.13, 13G.12, 14C.10, 14F.4, 14F.11, 15C.5, 15E.9, 15E.13
CLK: 10H.2, 11H.2, 12G.3, 14J.5, 15H.14
GAME_ON: 3J.1, 3J.13, 4J.1, 9E.13, 10B.10, 10D.5, 11C.1, 11C.4, 13F.2
GND: 1E.8, 1F.8, 2F.7, 2F.8, 3B.1, 3C.7, 3D.7, 3E.7, 3F.1, 3G.7, 3H.1, 3J.7, 4A.7, 4B.7, 4F.10, 4G.7, 4H.10, 4J.7, 5A.7, 5A.8, 5A.13, 5B.7, 5B.8, 5B.12, 5B.13, 5C.7, 5C.8, 5C.12, 5C.13, 5D.7, 5D.8, 5D.12, 5D.13, 5F.1, 5G.7, 5H.1, 5J.7, 6A.6, 6A.7, 6A.10, 6B.6, 6B.7, 6B.10, 6C.6, 6C.7, 6C.10, 6D.6, 6D.7, 6D.10, 6E.7, 6F.10, 6G.7, 6H.10, 6J.7, 7A.8, 7B.1, 7B.8, 7B.9, 7B.10, 7B.14, 7B.15, 7D.8, 7D.9, 7D.10, 7D.14, 7D.15, 7E.7, 7J.7, 8A.7, 8B.7, 8C.7, 8D.7, 8E.7, 8F.1, 8F.12, 8F.13, 8F.16, 8G.7, 8H.7, 9A.7, 9B.7, 9C.7, 9D.1, 9E.7, 9F.8, 9G.7, 9H.7, 9J.7, 10B.7, 10C.7, 10D.7, 10E.7, 10F.3, 10F.4, 10F.5, 10F.6, 10F.8, 10G.7, 10H.5, 10H.8, 10J.7, 11A.12, 11A.18, 11A.19, 11B.7, 11C.7, 11D.2, 11D.3, 11D.10, 11E.7, 11F.10, 11G.10, 11H.3, 11H.4, 11H.5, 11H.8, 11J.7, 12A.1, 12B.7, 12C.7, 12D.7, 12E.4, 12E.7, 12F.7, 12G.7, 12H.7, 12J.7, 13A.7, 13B.7, 13C.7, 13D.7, 13E.7, 13F.7, 13G.7, 13H.7, 13J.7, 14A.7, 14B.7, 14E.7, 14F.7, 14G.1, 14H.10, 14J.7, 15C.7, 15D.7, 15E.7, 15F.8, 15H.10, 15J.7
H1: 5J.1, 14B.4, 15H.1, 15H.12
H2: 5J.12, 8D.9, 9E.4, 13J.6, 14B.5, 15H.9
H4: 5J.9, 8D.10, 9E.5, 13J.5, 14D.9, 15H.8, 15J.5
H4_n: 14D.5, 15J.6
H8: 5J.2, 5J.5, 5J.10, 5J.13, 8C.9, 14D.10, 14H.14, 15H.11, 15J.3
H8_n: 8D.3, 8D.11, 8E.5, 14D.4, 15J.4
H16: 5A.11, 5B.11, 5C.11, 5D.11, 5J.4, 8H.11, 9B.6, 9B.9, 13H.12, 14D.2, 14D.13, 14H.1, 14H.12, 15J.1
H16_n: 9B.3, 9B.12, 9E.1, 15J.2
H32: 5A.10, 5B.10, 5C.10, 5D.10, 11A.23, 13H.10, 14H.9
H64: 5A.9, 5B.9, 5C.9, 5D.9, 10D.12, 10D.13, 11A.22, 13H.13, 13J.1, 14H.8
H128: 11A.21, 13J.11, 14H.11, 14J.12
H256: 11A.20, 13J.4, 14J.3
H256_n: 11E.8, 14J.2
HBLANK: 10B.5, 13H.1, 13H.6, 13H.9
HBLANK_n: 7J.13, 10H.10, 13H.3, 13H.4
HSYNC_n: 9F.2, 10F.2, 13H.8
V1: 3G.5, 3G.9, 5G.5, 5G.9, 11F.1, 11F.12, 12H.11, 14B.1, 14B.13
V2: 8C.10, 8D.5, 11F.9, 12F.9, 14B.2, 15B.1
V2_n: 12F.8, 15B.13
V4: 1F.13, 8C.11, 8D.4, 11F.8, 12H.5, 12H.10, 12J.5, 15B.2
V4_n: 12J.6, 15B.12
V8: 1F.3, 8B.2, 8B.4, 8B.10, 8C.5, 11F.11, 11G.14, 12F.13, 12J.3, 15B.4
V8_n: 8A.2, 8A.4, 8A.10, 9G.4, 12F.12, 15B.10
V16: 1F.1, 1F.15, 9G.5, 11E.6, 11G.1, 11G.12, 12F.5, 15B.5
V16_n: 12F.6, 15B.9
V32: 10C.4, 10C.11, 10C.13, 11G.9
V64: 10C.5, 10C.10, 11G.8, 12F.3
V64_n: 10C.1, 12F.4
V128: 10C.9, 11G.11, 11J.9, 12F.11
V128_n: 10C.2, 10C.3, 12F.10
V256: 11J.5, 12H.9
VBLANK: 11E.3, 11E.4, 12H.3, 14A.9, 15E.12
VCC: 3B.4, 3F.4, 3H.4, 3J.4, 3J.10, 3J.12, 4J.4, 5F.4, 5H.4, 7A.3, 7A.4, 7B.5, 7D.1, 7D.5, 7J.1, 7J.4, 8F.4, 8F.7, 8G.4, 8G.10, 8H.4, 8H.10, 8H.13, 9A.11, 9C.1, 9C.4, 9D.4, 9F.7, 10F.10, 10H.7, 11J.1, 12A.4, 12G.1, 12G.4, 12G.10, 13D.10, 14A.10, 14G.4
VRESET: 11E.2, 11E.9, 11F.2, 11F.3, 11G.2, 11G.3, 12D.10, 12D.13, 12G.8
VSYNC_n: 12H.6, 15F.5
